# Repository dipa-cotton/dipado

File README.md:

# dipado
it's a nintendo- but dipa instead of ninten
(do you get it?) (help its fine dw)
## process
i built this because i've always wanted to make a game console. I joined "make your own game console" back in march and like never started it, so this is kind of me reviving that. now that i think about it, this kind of looks like a sprig, except it has detachable controllers, joysticks, and connectors so that you can play it on the whole pcb or just seperate it- whatever works for you!
## how this works
you flash the firmware (located in firmware folder) to the chips- the xiao esp32c3 and the orpheus pico :3
once doing that, you can use the console to play a game by putting a chip into the tft display!
### bom
| Item | Quantity | Supplier | Cost per Item | Total Cost | Product Link |
| :--- | :---: | :--- | :---: | :---: | :--- |
| PCB | 1 | JLCPCB | $12.00 | $12.00 | [JLCPCB](https://jlcpcb.com) |
| ESP32-C3 Super Mini | 2 | Seeed Studio | $5.00 | $10.00 | [Product Link](https://www.seeedstudio.com/XIAO-ESP32S3-p-5627.html) |
| SJ1-3535NG | 1 | DigiKey | $2.00 | $2.00 | [Product Link](https://www.digikey.com/en/products/detail/same-sky-formerly-cui-devices-/SJ1-3535NG/738699) |
| TAS2505IRGER | 1 | Texas Instruments | $2.00 | $2.00 | [Product Link](https://www.ti.com/product/TAS2505/part-details/TAS2505IRGER) |
| Buzzer | 1 | Owned | $0.01 | $0.01 | N/A |
| Buttons | 8 | Owned | $0.01 | $0.08 | N/A |
| SW_SPDT | 3 | DigiKey | $0.58 | $1.74 | [Product Link](https://www.digikey.com/en/products/detail/same-sky-formerly-cui-devices-/SLW-913535-2A-SMT/21259974) |
| 1.8-inch LCD | 1 | AliExpress | $3.00 | $3.00 | [Product Link](https://www.aliexpress.us/item/3256809260879179.html) |
| Pogo Connectors | 4 | AliExpress | $3.25 | $13.00 | [Product Link](https://www.aliexpress.us/item/3256810202875535.html) |
| Joystick | 2 | DigiKey | $5.25 | $10.50 | [Product Link](https://www.digikey.com/en/products/detail/sparkfun-electronics/09032/6823623) |
| Estimated Shipping | 1 | N/A | $10.00 | $10.00 | N/A |
| **Total** | | | | **$64.33** | |
## pictures!

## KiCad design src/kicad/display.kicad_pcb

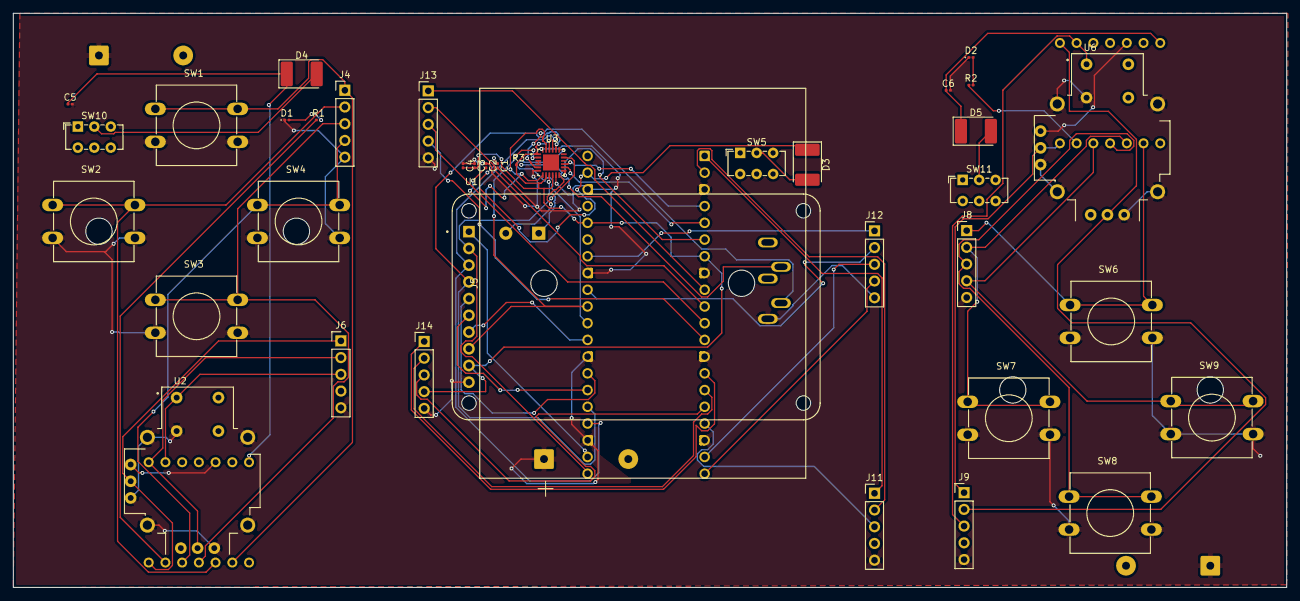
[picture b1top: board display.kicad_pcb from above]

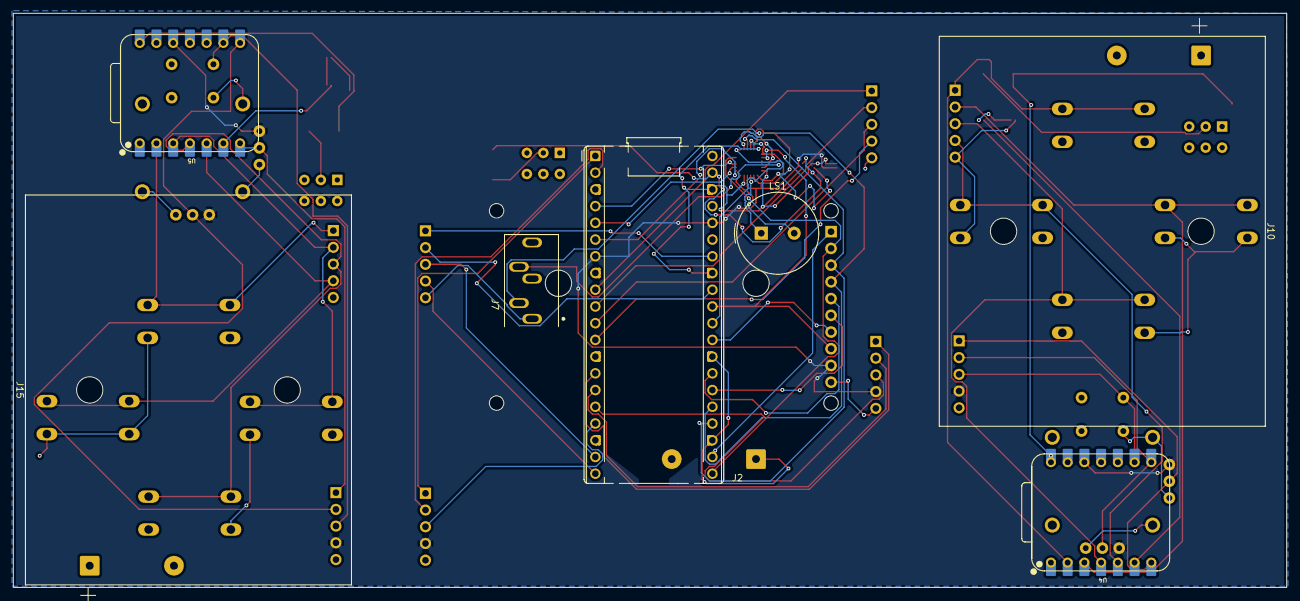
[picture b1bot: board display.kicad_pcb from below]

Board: 2 copper layers, 193.4 x 87.2 mm, 45 parts (7 on the bottom side), 44 nets.

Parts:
C1, C5, C6: C; C_0201_0603Metric
C2, C3: 0.1µF; C_0201_0603Metric
C4: 10µF; C_0201_0603Metric
D1, D2: LED; LED_0201_0603Metric
D3, D4, D5: D_Schottky; D_2114_3652Metric_Pad1.85x3.75mm_HandSolder
J2: Orpheus Pico; RaspberryPi_Pico_Common_THT
J4, J6, J8, J9, J11, J12, J13, J14: mag pogo; PinHeader_1x05_P2.54mm_Vertical
J5, J10, J15: battery; BatteryHolder_TruPower_BH-331P_3xAA
J7: SJ1-3535NG; CUI_SJ1-3535NG
LS1: Speaker; Buzzer_TDK_PS1240P02BT_D12.2mm_H6.5mm
R1, R2: 1k; R_0201_0603Metric
R3: 220; R_0201_0603Metric
SW1, SW2, SW3, SW4, SW6, SW7, SW8, SW9: SW_Push; SW_PUSH-12mm
SW5, SW10, SW11: SW_SPDT; SW_E-Switch_EG1271_SPDT
U1: 358; MODULE_358
U2, U6: COM-09032; XDCR_COM-09032
U3: TAS2505IRGER; QFN50P400X400X100-25N
U4, U5: XIAO_ESP32_S3; XIAO-ESP32-C3-DIP

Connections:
+3V3: C3.2, C4.2, J2.7, J2.36, J6.4, J9.4, J11.4, J14.4, R3.1, U1.9 (VCC), U2.H1 (H+), U2.V1 (V+), U3.1 (SPI_SEL), U3.8 (LDO_SEL), U3.10 (SPKVDD), U3.22 (IOVDD), U4.12 (3V3), U5.12 (3V3), U6.H1 (H+), U6.V1 (V+)
/A: J2.10, J4.2, J13.2, SW2.1, U4.3 (D2/GPIO3)
/BCLK: J2.4, U3.15 (BCLK)
/CARD_CS: J2.26, U1.6 (CARD_CS)
/CS: J2.30, U3.19 (SCL/SSZ)
/D: J2.12, J4.4, J13.4, SW4.1, U4.5 (D4/GPIO5)
/DC: J2.29, U1.7 (D/C)
/DIN: J2.6, U3.13 (DIN)
/HPOUT: J7.2, U3.5 (HPOUT)
/I: J2.34, J8.1, J12.1, SW6.1, U5.2 (D1/GPIO2)
/J: J2.32, J8.2, J12.2, SW7.1, U5.3 (D2/GPIO3)
/JOY: J2.14, J6.1, J14.1, U2.V2 (V), U4.7 (D6/GPIO43)
/JOY1: J2.1, J9.1, J11.1, U5.7 (D6/GPIO43), U6.V2 (V)
/JOY2: J2.15, J6.2, J14.2, U2.H2 (H), U4.8 (D7/GPIO44)
/JOY3: J2.16, J6.3, J14.3, U2.B1A (SEL+), U4.9 (D8/GPIO7)
/JOY4: J2.2, J9.2, J11.2, U5.8 (D7/GPIO44), U6.H2 (H)
/JOY5: J2.17, J9.3, J11.3, U5.9 (D8/GPIO7), U6.B1A (SEL+)
/K: J2.19, J8.3, J12.3, SW8.1, U5.4 (D3/GPIO4)
/L: J2.20, J8.4, J12.4, SW9.1, U5.5 (D4/GPIO5)
/LED1: R1.1, U4.6 (D5/GPIO6)
/LED2: R2.1, U5.6 (D5/GPIO6)
/LITE: J2.22, U1.1 (LITE)
/MISO: J2.21, U1.2 (MISO), U3.17 (MISO)
/MOSI: J2.25, U1.4 (MOSI), U3.20 (SDA/MOSI)
/RESET: J2.31, U1.8 (RESET), U3.2 (RST)
/S: J2.11, J4.3, J13.3, SW3.1, U4.4 (D3/GPIO4)
/SCK: J2.24, U1.3 (SCK), U3.21 (SCLK)
/TFT_CS: J2.27, U1.5 (TFT_CS)
/W: J2.9, J4.1, J13.1, SW1.1, U4.2 (D1/GPIO2)
/WCLK: J2.5, U3.14 (WCLK)
GND: C1.2, C2.1, C3.1, C4.1, C5.2, C6.2, D1.1 (K), D2.1 (K), J2.3, J2.8, J2.13, J2.18, J2.23, J2.28, J2.33, J2.38, J4.5, J5.1, J6.5, J7.1, J8.5, J9.5, J10.1, J11.5, J12.5, J13.5, J14.5, J15.1, SW1.2, SW2.2, SW3.2, SW4.2, SW6.2, SW7.2, SW8.2, SW9.2, U1.10 (GND), U2.B2A (SEL-), U2.H3 (H-), U2.S1 (SHIELD), U2.S2 (SHIELD), U2.S3 (SHIELD), U2.S4 (SHIELD), U2.V3 (V-), U3.6 (AVSS), U3.11 (SPKVSS), U3.24 (DVSS), U6.B2A (SEL-), U6.H3 (H-), U6.S1 (SHIELD), U6.S2 (SHIELD), U6.S3 (SHIELD), U6.S4 (SHIELD), U6.V3 (V-)
unnamed: D1.2 (A), R1.2
unnamed: D2.2 (A), R2.2
unnamed: D3.2 (A), SW5.2 (B)
unnamed: C1.1, D3.1 (K), J2.39
unnamed: D4.2 (A), SW10.2 (B)
unnamed: C5.1, D4.1 (K), U4.14 (5V)
unnamed: D5.2 (A), SW11.2 (B)
unnamed: C6.1, D5.1 (K), U5.14 (5V)
unnamed: J7.3, R3.2
unnamed: U3.3 (AINL), U3.4 (AINR)
unnamed: C2.2, U3.7 (AVDD), U3.23 (DVDD)
unnamed: LS1.1, U3.9 (SPKM)
unnamed: LS1.2, U3.12 (SPKP)

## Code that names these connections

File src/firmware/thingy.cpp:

#include <Arduino.h>

const int PIN_W = 1; // D0 GPIO1
const int PIN_A = 2; // D1 GPIO2
const int PIN_S = 3; // D2 GPIO3
const int PIN_D = 4; // D3 GPIO4

const int PIN_I = 1; // D0 GPIO1
const int PIN_J = 2; // D1 GPIO2
const int PIN_K = 3; // D2 GPIO3
const int PIN_L = 4; // D3 GPIO4

const int PIN_JOY_V = 7; // JOY
const int PIN_JOY_H = 8; // JOY2
const int PIN_JOY_BTN = 9; // JOY3

const int PIN_JOY2_V = 7; // JOY1
const int PIN_JOY2_H = 8; // JOY4
const int PIN_JOY2_BTN = 9; // JOY5

void setup() {
Serial.begin(115200);
delay(1000);

pinMode(PIN_W, INPUT_PULLUP);
pinMode(PIN_A, INPUT_PULLUP);
pinMode(PIN_S, INPUT_PULLUP);
pinMode(PIN_D, INPUT_PULLUP);
pinMode(PIN_I, INPUT_PULLUP);
pinMode(PIN_J, INPUT_PULLUP);
pinMode(PIN_K, INPUT_PULLUP);
pinMode(PIN_L, INPUT_PULLUP);
pinMode(PIN_JOY2_V, INPUT);
pinMode(PIN_JOY2_H, INPUT);
pinMode(PIN_JOY2_BTN, INPUT_PULLUP);
pinMode(PIN_JOY_BTN, INPUT_PULLUP);
pinMode(PIN_JOY2_BTN, INPUT_PULLUP);
pinMode(PIN_JOY_V, INPUT);
pinMode(PIN_JOY_H, INPUT);
pinMode(PIN_JOY_BTN, INPUT_PULLUP);

Serial.println("this works");
}

void loop() {
bool stateW = digitalRead(PIN_W) == LOW;
bool stateA = digitalRead(PIN_A) == LOW;
bool stateS = digitalRead(PIN_S) == LOW;
bool stateD = digitalRead(PIN_D) == LOW;
bool stateI = digitalRead(PIN_I) == LOW;
bool stateJ = digitalRead(PIN_J) == LOW;
bool stateK = digitalRead(PIN_K) == LOW;
bool stateL = digitalRead(PIN_L) == LOW;

int joyV = analogRead(PIN_JOY_V);
int joyH = analogRead(PIN_JOY_H);
bool joyBtn = digitalRead(PIN_JOY_BTN) == LOW;

int joy2V = analogRead(PIN_JOY2_V);
int joy2H = analogRead(PIN_JOY2_H);
bool joy2Btn = digitalRead(PIN_JOY2_BTN) == LOW;

Serial.printf("Buttons -> W:%d A:%d S:%d D:%d I:%d J:%d K:%d L:%d | Joystick -> V:%d, H:%d, Btn:%d | Joystick2 -> V:%d, H:%d, Btn:%d\n", 
                stateW, stateA, stateS, stateD, stateI, stateJ, stateK, stateL, joyV, joyH, joyBtn, joy2V, joy2H, joy2Btn);


  delay(50);
}
